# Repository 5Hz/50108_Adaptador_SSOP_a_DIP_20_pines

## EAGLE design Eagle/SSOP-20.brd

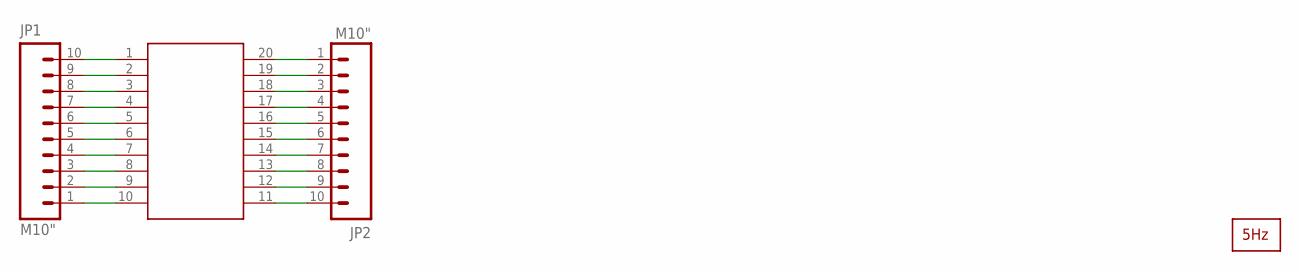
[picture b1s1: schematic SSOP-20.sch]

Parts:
JP1, JP2: M10"; 1X10
U$1: SSOP-20SSOP-20; SSOP-20
U$2: LOGO2_SILK10MM; LOGO2_10MM

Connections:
unnamed: JP1.1, U$1.10
unnamed: JP1.2, U$1.9
unnamed: JP1.3, U$1.8
unnamed: JP1.4, U$1.7
unnamed: JP1.5, U$1.6
unnamed: JP1.6, U$1.5
unnamed: JP1.7, U$1.4
unnamed: JP1.8, U$1.3
unnamed: JP1.9, U$1.2
unnamed: JP1.10, U$1.1
unnamed: JP2.1, U$1.20
unnamed: JP2.2, U$1.19
unnamed: JP2.3, U$1.18
unnamed: JP2.4, U$1.17
unnamed: JP2.5, U$1.16
unnamed: JP2.6, U$1.15
unnamed: JP2.7, U$1.14
unnamed: JP2.8, U$1.13
unnamed: JP2.9, U$1.12
unnamed: JP2.10, U$1.11

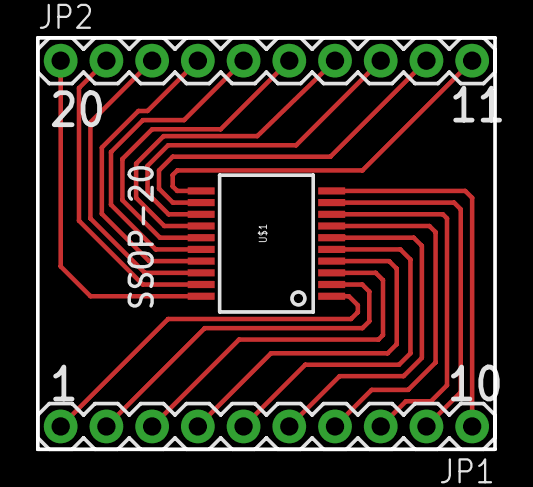
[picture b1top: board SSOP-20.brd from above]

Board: 2 copper layers, 25.4 x 22.9 mm, 4 parts (1 on the bottom side), 20 nets.

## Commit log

2014-01-14 creación

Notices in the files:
parts and their libraries:
SparkFun: Licensing: CC v3.0 Share-Alike You are welcome to use this library for commercial purposes.
